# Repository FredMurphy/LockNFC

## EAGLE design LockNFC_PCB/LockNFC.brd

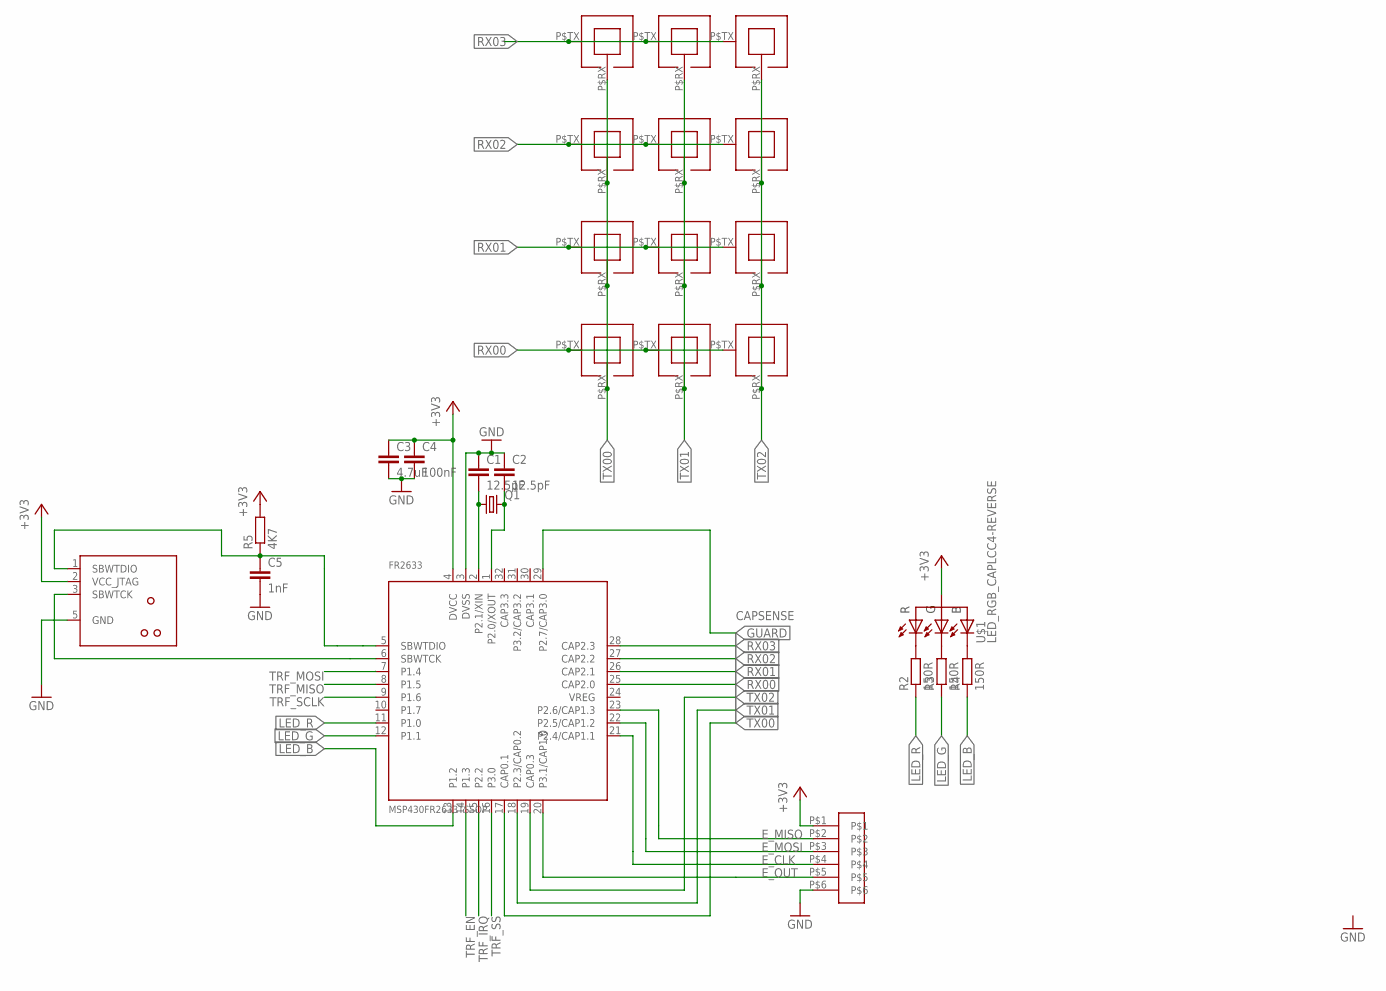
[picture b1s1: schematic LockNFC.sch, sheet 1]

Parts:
C1, C2: 12.5pF; C0805
C3: 4.7uF; C0805
C4: 100nF; C0805
C5: 1nF; C0805
FR2633: MSP430FR2633TSSOP; TSSOP(DA)32
J1: TC2030-MSP430-NO-UART-NL; TC2030-MSP430-NL-NO-UART
Q1: CRYSTALFC-135; FC-135
R2, R3, R4: 150R; R0603
R5: 4K7; R0603
U$1: LED_RGB_CAPLCC4-REVERSE; PLCC4-REVERSE
U$2, U$3, U$4, U$5, U$6, U$7, U$8, U$9, U$10, U$11, U$12, U$13: CAP_MUTUAL_SMALL
U$14: 1X6_SMD_HEADER; 1X6-SMD-1.27MM

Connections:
+3V3: C3.1, C4.1, FR2633.4 (DVCC), J1.2 (VCC_JTAG), R5.2, U$1.P$2 (A), U$14.P$1; also elsewhere on the board
E_CLK: FR2633.21 (P2.4/CAP1.1), U$14.P$4
E_MISO: FR2633.23 (P2.6/CAP1.3), U$14.P$2
E_MOSI: FR2633.22 (P2.5/CAP1.2), U$14.P$3
E_OUT: FR2633.20 (P3.1/CAP1.0), U$14.P$5
GND: C1.1, C2.1, C3.2, C4.2, C5.2, FR2633.3 (DVSS), J1.5 (GND), U$14.P$6; also elsewhere on the board
GUARD: FR2633.29 (P2.7/CAP3.0)
LED_B: FR2633.13 (P1.2), R4.1
LED_G: FR2633.12 (P1.1), R3.1
LED_R: FR2633.11 (P1.0), R2.1
unnamed: R2.2, U$1.P$1 (C_RED)
unnamed: R3.2, U$1.P$4 (C_GREEN)
unnamed: R4.2, U$1.P$3 (C_BLUE)
P1.7: FR2633.10 (P1.7)
RX00: FR2633.25 (CAP2.0), U$11.P$TX (TX), U$12.P$TX (TX), U$13.P$TX (TX)
RX01: FR2633.26 (CAP2.1), U$8.P$TX (TX), U$9.P$TX (TX), U$10.P$TX (TX)
RX02: FR2633.27 (CAP2.2), U$5.P$TX (TX), U$6.P$TX (TX), U$7.P$TX (TX)
RX03: FR2633.28 (CAP2.3), U$2.P$TX (TX), U$3.P$TX (TX), U$4.P$TX (TX)
SBWTCK: FR2633.6 (SBWTCK), J1.3 (SBWTCK)
SBWTDIO: C5.1, FR2633.5 (SBWTDIO), J1.1 (SBWTDIO), R5.1
TRF_EN: FR2633.14 (P1.3); also elsewhere on the board
TRF_IRQ: FR2633.15 (P2.2); also elsewhere on the board
TRF_MISO: FR2633.8 (P1.5); also elsewhere on the board
TRF_MOSI: FR2633.7 (P1.4); also elsewhere on the board
TRF_SCLK: FR2633.9 (P1.6); also elsewhere on the board
TRF_SS: FR2633.16 (P3.0); also elsewhere on the board
TX00: FR2633.17 (CAP0.1), U$2.P$RX (RX), U$5.P$RX (RX), U$8.P$RX (RX), U$11.P$RX (RX)
TX01: FR2633.18 (P2.3/CAP0.2), U$3.P$RX (RX), U$6.P$RX (RX), U$9.P$RX (RX), U$12.P$RX (RX)
TX02: FR2633.19 (CAP0.3), U$4.P$RX (RX), U$7.P$RX (RX), U$10.P$RX (RX), U$13.P$RX (RX)
XIN: C1.2, FR2633.2 (P2.1/XIN), Q1.1
XOUT: C2.2, FR2633.1 (P2.0/XOUT), Q1.2

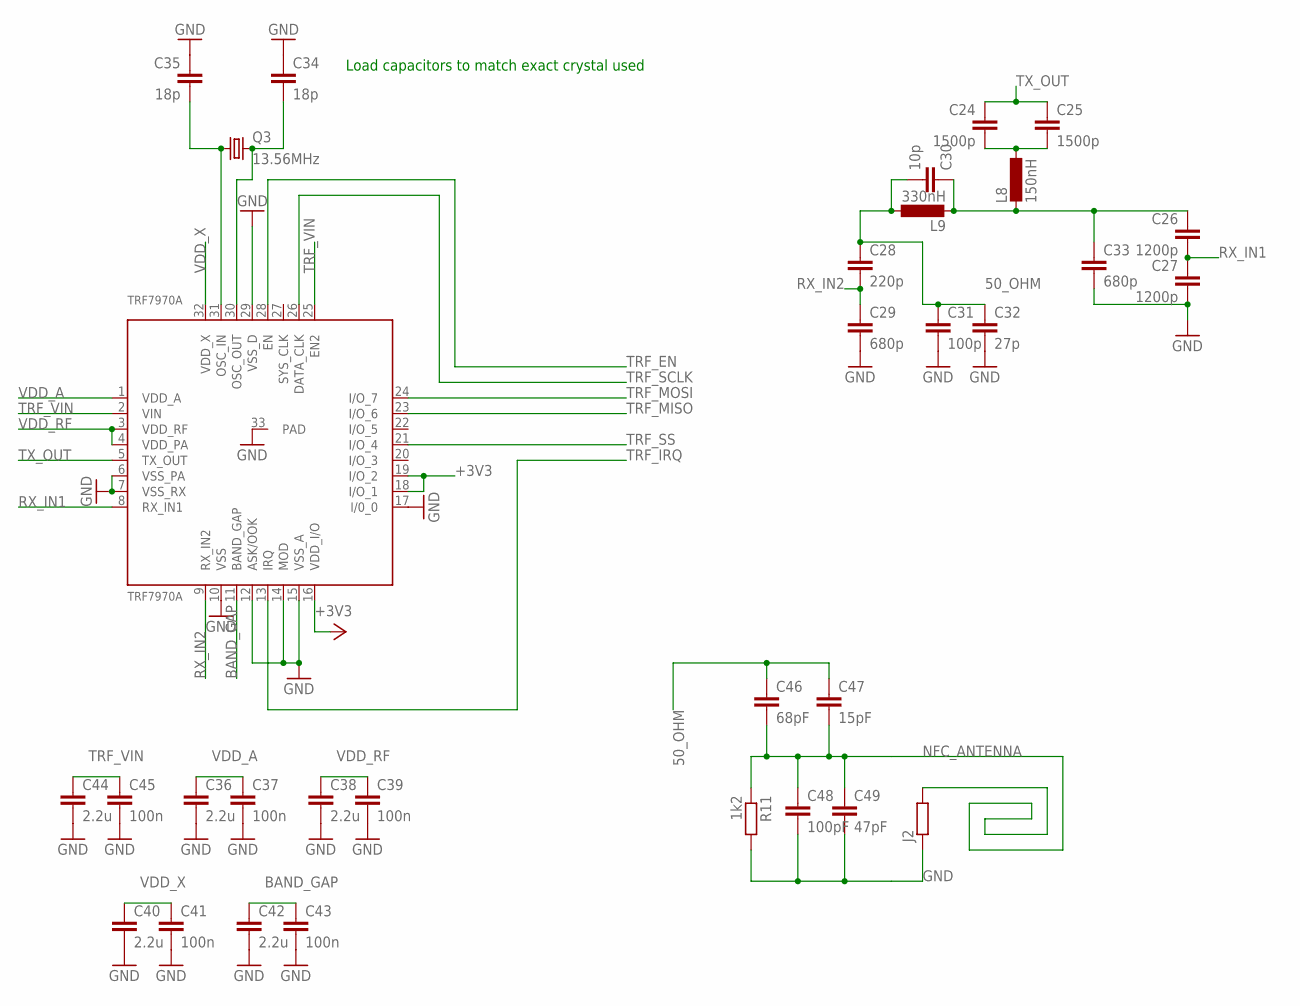
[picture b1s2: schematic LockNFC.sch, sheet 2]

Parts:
C24, C25: 1500p; C0805
C26, C27: 1200p; C0805
C28: 220p; C0805
C29, C33: 680p; C0805
C30: 10p; C0805
C31: 100p; C0805
C32: 27p; C0805
C34, C35: 18p; C0805
C36, C38, C40, C42, C44: 2.2u; C0805
C37, C39, C41, C43, C45: 100n; C0805
C46: 68pF; C0805
C47: 15pF; C0805
C48: 100pF; C0805
C49: 47pF; C0805
J2: R-EU_R0402; R0402
L8: 150nH; L1008
L9: 330nH; L1008
Q3: 13.56MHz; CRYSTAL_TCX
R11: 1k2; R0805
TRF7970A: TRF7970A; QFN(RHB)32

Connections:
50_OHM: C28.1, C30.2, C31.1, C32.1, C46.1, C47.1, L9.1
+3V3: TRF7970A.16 (VDD_I/O), TRF7970A.18 (I/O_1), TRF7970A.19 (I/O_2); also elsewhere on the board
BAND_GAP: C42.1, C43.1, TRF7970A.11 (BAND_GAP)
GND: C27.2, C29.2, C31.2, C32.2, C33.2, C34.1, C35.1, C36.2, C37.2, C38.2, C39.2, C40.2, C41.2, C42.2, C43.2, C44.2, C45.2, C48.2, C49.2, J2.1, R11.2, TRF7970A.6 (VSS_PA), TRF7970A.7 (VSS_RX), TRF7970A.10 (VSS), TRF7970A.12 (ASK/OOK), TRF7970A.14 (MOD), TRF7970A.15 (VSS_A), TRF7970A.17 (I/0_0), TRF7970A.29 (VSS_D), TRF7970A.33 (PAD); also elsewhere on the board
unnamed: C24.2, C25.2, L8.1
unnamed: C26.1, C30.1, C33.1, L8.2, L9.2
unnamed: C35.2, Q3.1, TRF7970A.31 (OSC_IN)
unnamed: C34.2, Q3.2, TRF7970A.30 (OSC_OUT)
NFC_ANTENNA: C46.2, C47.2, C48.1, C49.1, J2.2, R11.1
RX_IN1: C26.2, C27.1, TRF7970A.8 (RX_IN1)
RX_IN2: C28.2, C29.1, TRF7970A.9 (RX_IN2)
TRF_EN: TRF7970A.28 (EN); also elsewhere on the board
TRF_IRQ: TRF7970A.13 (IRQ); also elsewhere on the board
TRF_MISO: TRF7970A.23 (I/O_6); also elsewhere on the board
TRF_MOSI: TRF7970A.24 (I/O_7); also elsewhere on the board
TRF_SCLK: TRF7970A.26 (DATA_CLK); also elsewhere on the board
TRF_SS: TRF7970A.21 (I/O_4); also elsewhere on the board
TRF_VIN: C44.1, C45.1, TRF7970A.2 (VIN), TRF7970A.25 (EN2)
TX_OUT: C24.1, C25.1, TRF7970A.5 (TX_OUT)
VDD_A: C36.1, C37.1, TRF7970A.1 (VDD_A)
VDD_RF: C38.1, C39.1, TRF7970A.3 (VDD_RF), TRF7970A.4 (VDD_PA)
VDD_X: C40.1, C41.1, TRF7970A.32 (VDD_X)

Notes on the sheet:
Load capacitors to match exact crystal used

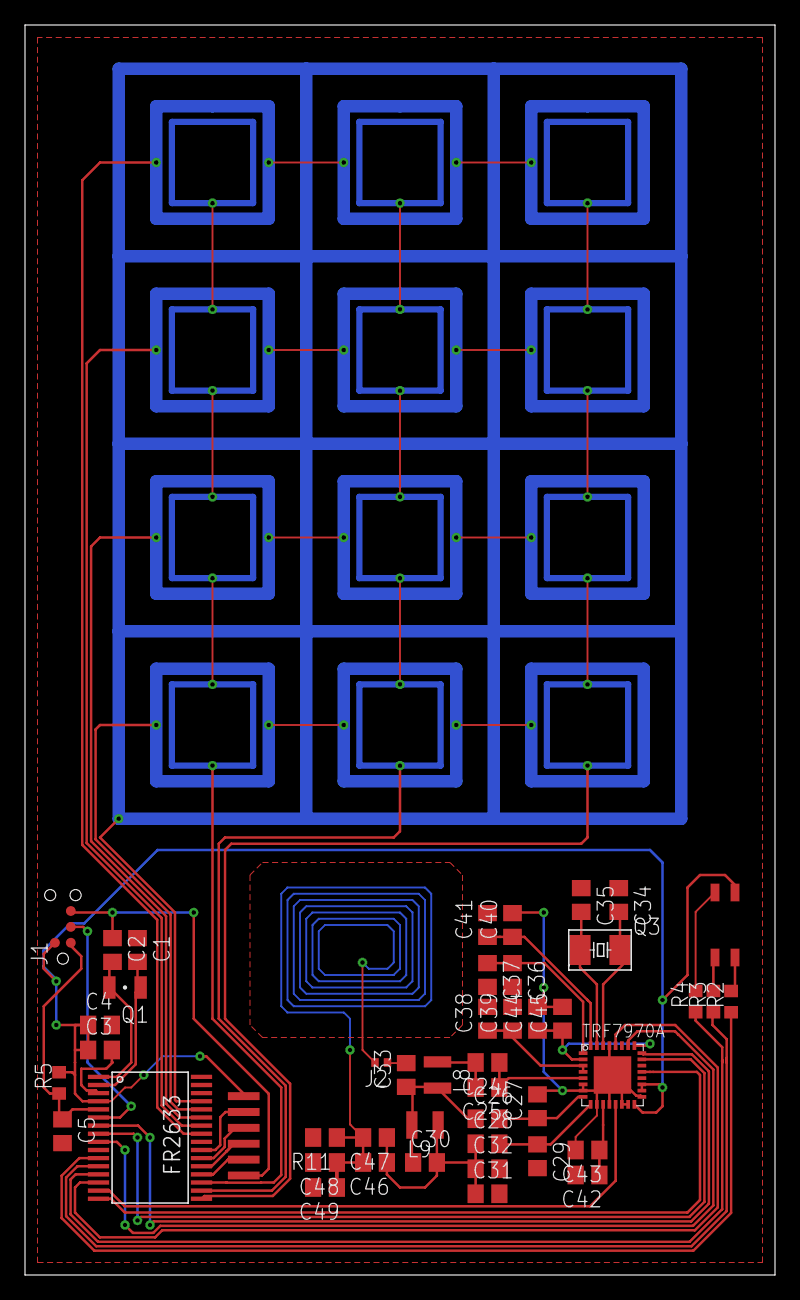
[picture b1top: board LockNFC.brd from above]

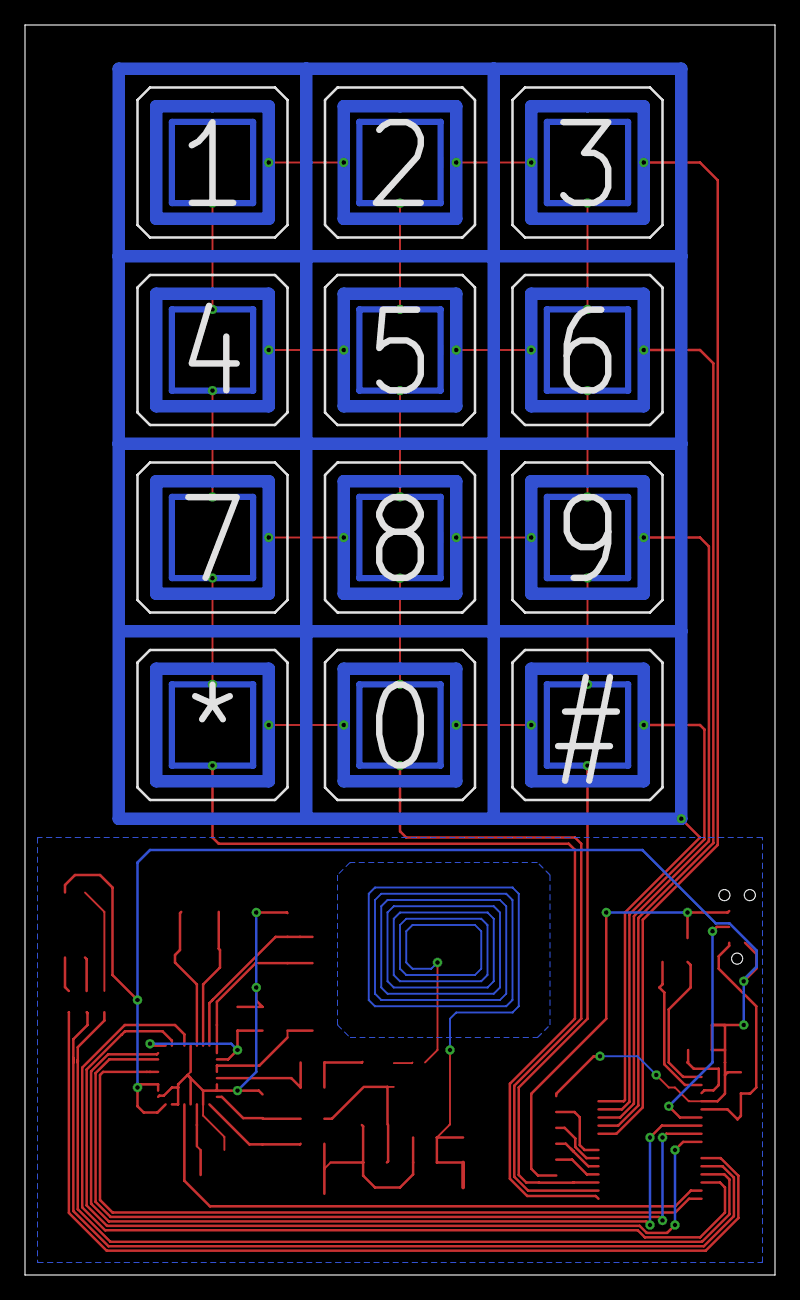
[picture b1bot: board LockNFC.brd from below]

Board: 2 copper layers, 60.0 x 100.0 mm, 58 parts (12 on the bottom side), 43 nets.

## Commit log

2018-12-17 Initial commit after getting CCS breakpoints working
2018-12-20 Timer working
2018-12-23 Eagle PCB and library
2018-12-23 Removed notes
2019-02-13 3D models for enclosure and limit switches inside Yale lock
2019-02-16 Compares with a list of valid codes - so the boys can have their own
2019-03-03 Valid code/tag then choose a door (1 or 2) to open
2019-03-05 Tweaks for battery life improvements
2019-03-29 Performance over power saving. 3 = both doors (for Daniel).
2019-05-16 Diabled wake on proximity for now

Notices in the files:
parts and their libraries:
tag-connect-msp430: ©2009 ROFA.cz - modified and updated by Robert Darlington ‹rdarlington@gmail.com›
tag-connect-msp430: ©2014 Fred - adapted from TagConnect's MCP version.
